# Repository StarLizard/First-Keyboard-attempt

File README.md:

Trying to design my own Bluetooth Keyboard pcb with Hotswap MX Switches

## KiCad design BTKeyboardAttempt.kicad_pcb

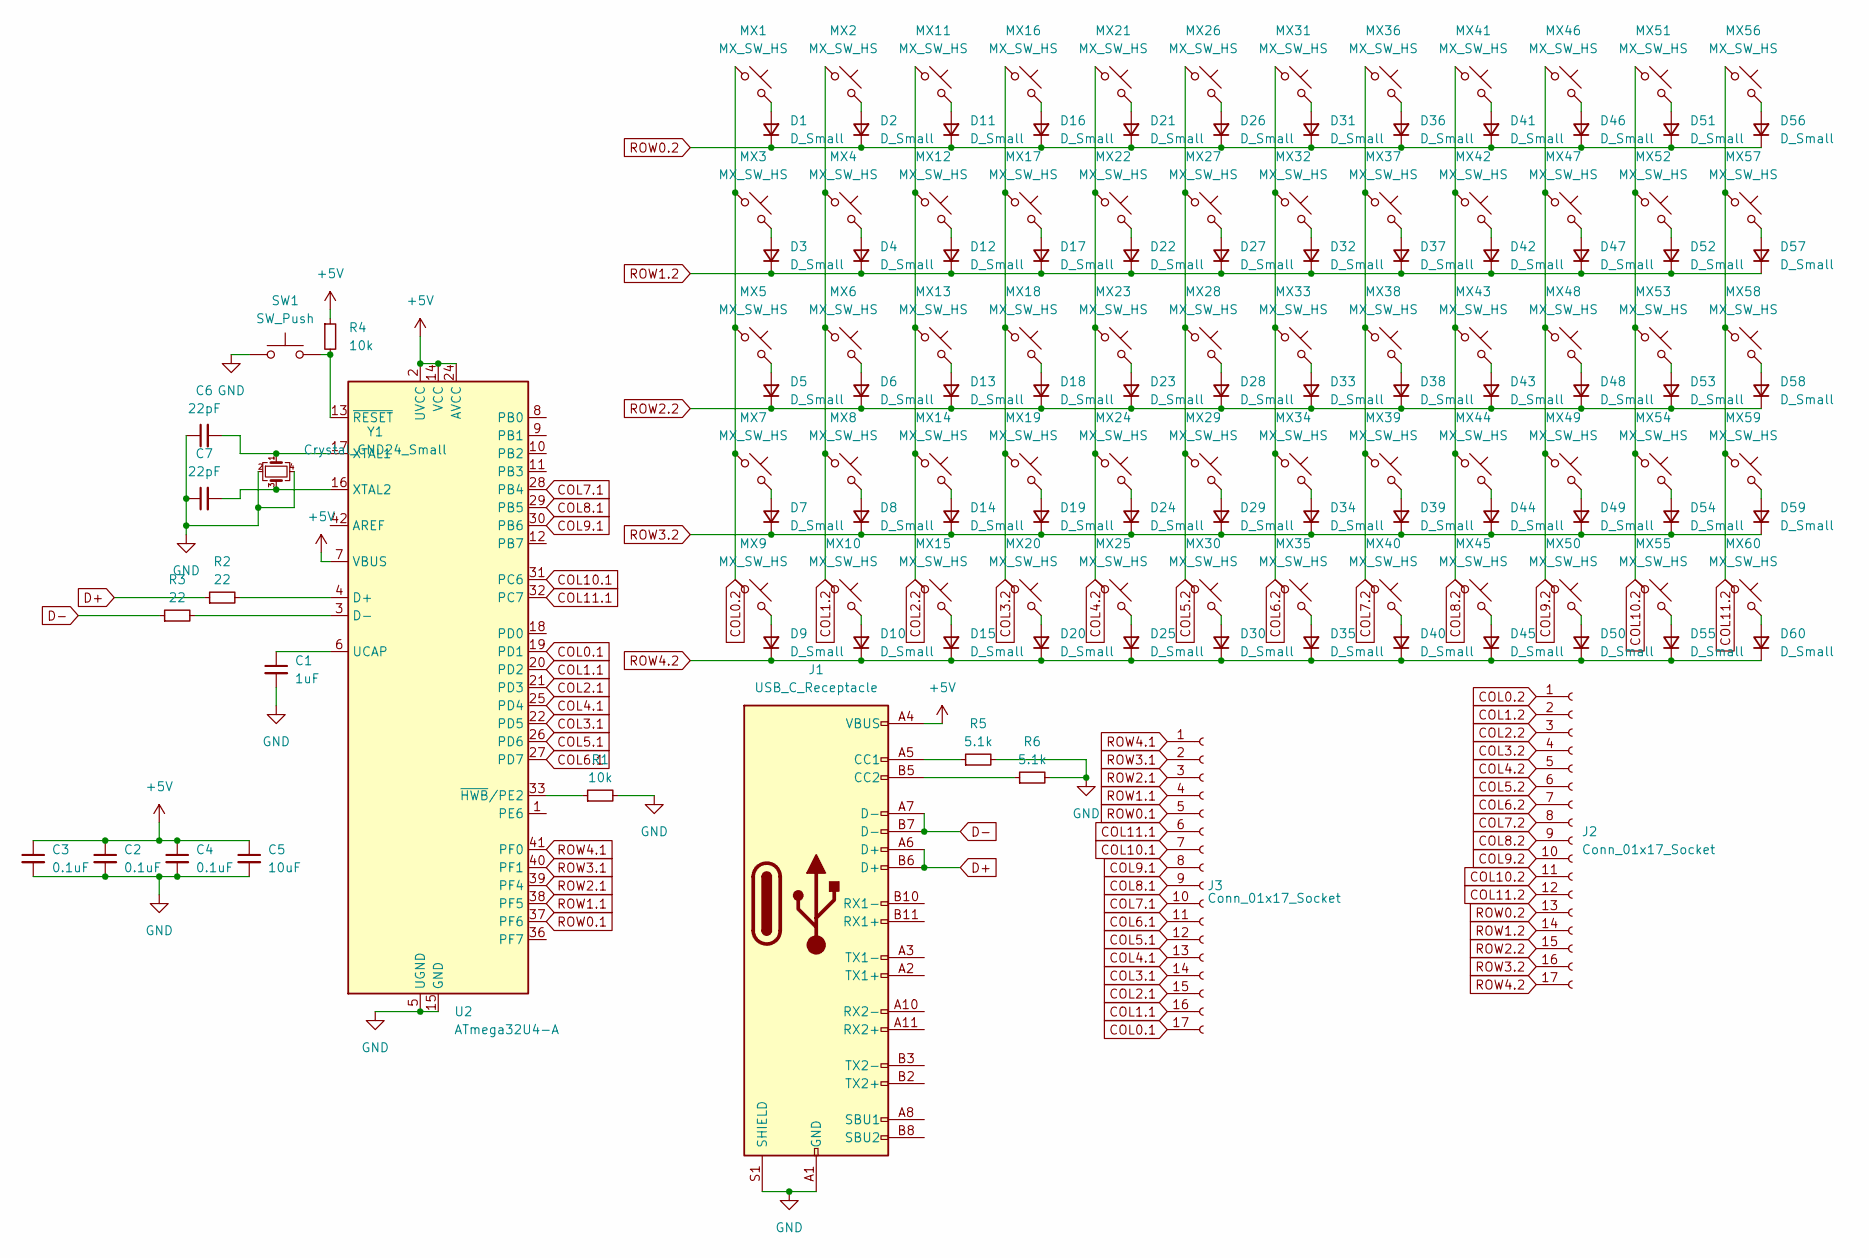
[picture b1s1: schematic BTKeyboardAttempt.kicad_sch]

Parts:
C1: 1uF; C_0805_2012Metric
C2, C3, C4: 0.1uF; C_0805_2012Metric
C5: 10uF; C_0805_2012Metric
C6, C7: 22pF; C_0805_2012Metric
D1, D2, D3, D4, D5, D6, D7, D8, D9, D10, D11, D12, D13, D14, D15, D16, D17, D18, D19, D20, D21, D22, D23, D24, D25, D26, D27, D28, D29, D30, D31, D32, D33, D34, D35, D36, D37, D38, D39, D40, D41, D42, D43, D44, D45, D46, D47, D48, D49, D50, D51, D52, D53, D54, D55, D56, D57, D58, D59, D60: D_Small; D_SOD-123
J1: USB_C_Receptacle; USB_C_Receptacle_Amphenol_12401548E4-2A
J2, J3: Conn_01x17_Socket; PinHeader_1x17_P1.00mm_Horizontal
MX1, MX2, MX3, MX4, MX5, MX6, MX7, MX8, MX9, MX10, MX11, MX12, MX13, MX14, MX15, MX16, MX17, MX18, MX19, MX20, MX21, MX22, MX23, MX24, MX25, MX26, MX27, MX28, MX29, MX30, MX31, MX32, MX33, MX34, MX35, MX36, MX37, MX38, MX39, MX40, MX41, MX42, MX43, MX44, MX45, MX46, MX47, MX48, MX49, MX50, MX51, MX52, MX53, MX54, MX55, MX56, MX57, MX58, MX59, MX60: MX_SW_HS; SW_MX_HS_CPG151101S11_1u
R1, R4: 10k; R_0805_2012Metric
R2, R3: 22; R_0805_2012Metric
R5, R6: 5.1k; R_0805_2012Metric
SW1: SW_Push; SKQG-1155865
U2: ATmega32U4-A; TQFP-44_10x10mm_P0.8mm
Y1: Crystal_GND24_Small; Crystal_SMD_3225-4Pin_3.2x2.5mm

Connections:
+5V: C2.1, C3.1, C4.1, C5.1, J1.A4 (VBUS), J1.A9 (VBUS), J1.B4 (VBUS), J1.B9 (VBUS), R4.1, U2.2 (UVCC), U2.7 (VBUS), U2.14 (VCC), U2.24 (AVCC), U2.34 (VCC), U2.44 (AVCC)
COL0.1: J3.17, U2.19 (PD1)
COL0.2: J2.1, MX1.1, MX3.1, MX5.1, MX7.1, MX9.1
COL1.1: J3.16, U2.20 (PD2)
COL1.2: J2.2, MX2.1, MX4.1, MX6.1, MX8.1, MX10.1
COL2.1: J3.15, U2.21 (PD3)
COL2.2: J2.3, MX11.1, MX12.1, MX13.1, MX14.1, MX15.1
COL3.1: J3.14, U2.22 (PD5)
COL3.2: J2.4, MX16.1, MX17.1, MX18.1, MX19.1, MX20.1
COL4.1: J3.13, U2.25 (PD4)
COL4.2: J2.5, MX21.1, MX22.1, MX23.1, MX24.1, MX25.1
COL5.1: J3.12, U2.26 (PD6)
COL5.2: J2.6, MX26.1, MX27.1, MX28.1, MX29.1, MX30.1
COL6.1: J3.11, U2.27 (PD7)
COL6.2: J2.7, MX31.1, MX32.1, MX33.1, MX34.1, MX35.1
COL7.1: J3.10, U2.28 (PB4)
COL7.2: J2.8, MX36.1, MX37.1, MX38.1, MX39.1, MX40.1
COL8.1: J3.9, U2.29 (PB5)
COL8.2: J2.9, MX41.1, MX42.1, MX43.1, MX44.1, MX45.1
COL9.1: J3.8, U2.30 (PB6)
COL9.2: J2.10, MX46.1, MX47.1, MX48.1, MX49.1, MX50.1
COL10.1: J3.7, U2.31 (PC6)
COL10.2: J2.11, MX51.1, MX52.1, MX53.1, MX54.1, MX55.1
COL11.1: J3.6, U2.32 (PC7)
COL11.2: J2.12, MX56.1, MX57.1, MX58.1, MX59.1, MX60.1
D+: J1.A6 (D+), J1.B6 (D+), R2.1
D-: J1.A7 (D-), J1.B7 (D-), R3.1
GND: C1.2, C2.2, C3.2, C4.2, C5.2, C6.1, C7.1, J1.A1 (GND), J1.A12 (GND), J1.B1 (GND), J1.B12 (GND), J1.S1 (SHIELD), R1.2, R5.2, R6.2, SW1.1, U2.5 (UGND), U2.15 (GND), U2.23 (GND), U2.35 (GND), U2.43 (GND), Y1.2, Y1.4
unnamed: D1.2 (A), MX1.2
unnamed: D2.2 (A), MX2.2
unnamed: D3.2 (A), MX3.2
unnamed: D4.2 (A), MX4.2
unnamed: D5.2 (A), MX5.2
unnamed: D6.2 (A), MX6.2
unnamed: D7.2 (A), MX7.2
unnamed: D8.2 (A), MX8.2
unnamed: D9.2 (A), MX9.2
unnamed: D10.2 (A), MX10.2
unnamed: D11.2 (A), MX11.2
unnamed: D12.2 (A), MX12.2
unnamed: D13.2 (A), MX13.2
unnamed: D14.2 (A), MX14.2
unnamed: D15.2 (A), MX15.2
unnamed: D16.2 (A), MX16.2
unnamed: D17.2 (A), MX17.2
unnamed: D18.2 (A), MX18.2
unnamed: D19.2 (A), MX19.2
unnamed: D20.2 (A), MX20.2
unnamed: D21.2 (A), MX21.2
unnamed: D22.2 (A), MX22.2
unnamed: D23.2 (A), MX23.2
unnamed: D24.2 (A), MX24.2
unnamed: D25.2 (A), MX25.2
unnamed: D26.2 (A), MX26.2
unnamed: D27.2 (A), MX27.2
unnamed: D28.2 (A), MX28.2
unnamed: D29.2 (A), MX29.2
unnamed: D30.2 (A), MX30.2
unnamed: D31.2 (A), MX31.2
unnamed: D32.2 (A), MX32.2
unnamed: D33.2 (A), MX33.2
unnamed: D34.2 (A), MX34.2
unnamed: D35.2 (A), MX35.2
unnamed: D36.2 (A), MX36.2
unnamed: D37.2 (A), MX37.2
unnamed: D38.2 (A), MX38.2
unnamed: D39.2 (A), MX39.2
unnamed: D40.2 (A), MX40.2
unnamed: D41.2 (A), MX41.2
unnamed: D42.2 (A), MX42.2
unnamed: D43.2 (A), MX43.2
unnamed: D44.2 (A), MX44.2
unnamed: D45.2 (A), MX45.2
unnamed: D46.2 (A), MX46.2
unnamed: D47.2 (A), MX47.2
unnamed: D48.2 (A), MX48.2
unnamed: D49.2 (A), MX49.2
unnamed: D50.2 (A), MX50.2
unnamed: D51.2 (A), MX51.2
unnamed: D52.2 (A), MX52.2
unnamed: D53.2 (A), MX53.2
unnamed: D54.2 (A), MX54.2
unnamed: D55.2 (A), MX55.2
unnamed: D56.2 (A), MX56.2
unnamed: D57.2 (A), MX57.2
unnamed: D58.2 (A), MX58.2
unnamed: D59.2 (A), MX59.2
unnamed: D60.2 (A), MX60.2
unnamed: J1.A5 (CC1), R5.1
unnamed: J1.B5 (CC2), R6.1
unnamed: R2.2, U2.4 (D+)
unnamed: R3.2, U2.3 (D-)
unnamed: C1.1, U2.6 (UCAP)
unnamed: C6.2, U2.17 (XTAL1), Y1.1
unnamed: C7.2, U2.16 (XTAL2), Y1.3
unnamed: R1.1, U2.33 (~HWB/PE2)
unnamed: R4.2, SW1.2, U2.13 (~RESET)
ROW0.1: J3.5, U2.37 (PF6)
ROW0.2: D1.1 (K), D2.1 (K), D11.1 (K), D16.1 (K), D21.1 (K), D26.1 (K), D31.1 (K), D36.1 (K), D41.1 (K), D46.1 (K), D51.1 (K), D56.1 (K), J2.13
ROW1.1: J3.4, U2.38 (PF5)
ROW1.2: D3.1 (K), D4.1 (K), D12.1 (K), D17.1 (K), D22.1 (K), D27.1 (K), D32.1 (K), D37.1 (K), D42.1 (K), D47.1 (K), D52.1 (K), D57.1 (K), J2.14
ROW2.1: J3.3, U2.39 (PF4)
ROW2.2: D5.1 (K), D6.1 (K), D13.1 (K), D18.1 (K), D23.1 (K), D28.1 (K), D33.1 (K), D38.1 (K), D43.1 (K), D48.1 (K), D53.1 (K), D58.1 (K), J2.15
ROW3.1: J3.2, U2.40 (PF1)
ROW3.2: D7.1 (K), D8.1 (K), D14.1 (K), D19.1 (K), D24.1 (K), D29.1 (K), D34.1 (K), D39.1 (K), D44.1 (K), D49.1 (K), D54.1 (K), D59.1 (K), J2.16
ROW4.1: J3.1, U2.41 (PF0)
ROW4.2: D9.1 (K), D10.1 (K), D15.1 (K), D20.1 (K), D25.1 (K), D30.1 (K), D35.1 (K), D40.1 (K), D45.1 (K), D50.1 (K), D55.1 (K), D60.1 (K), J2.17

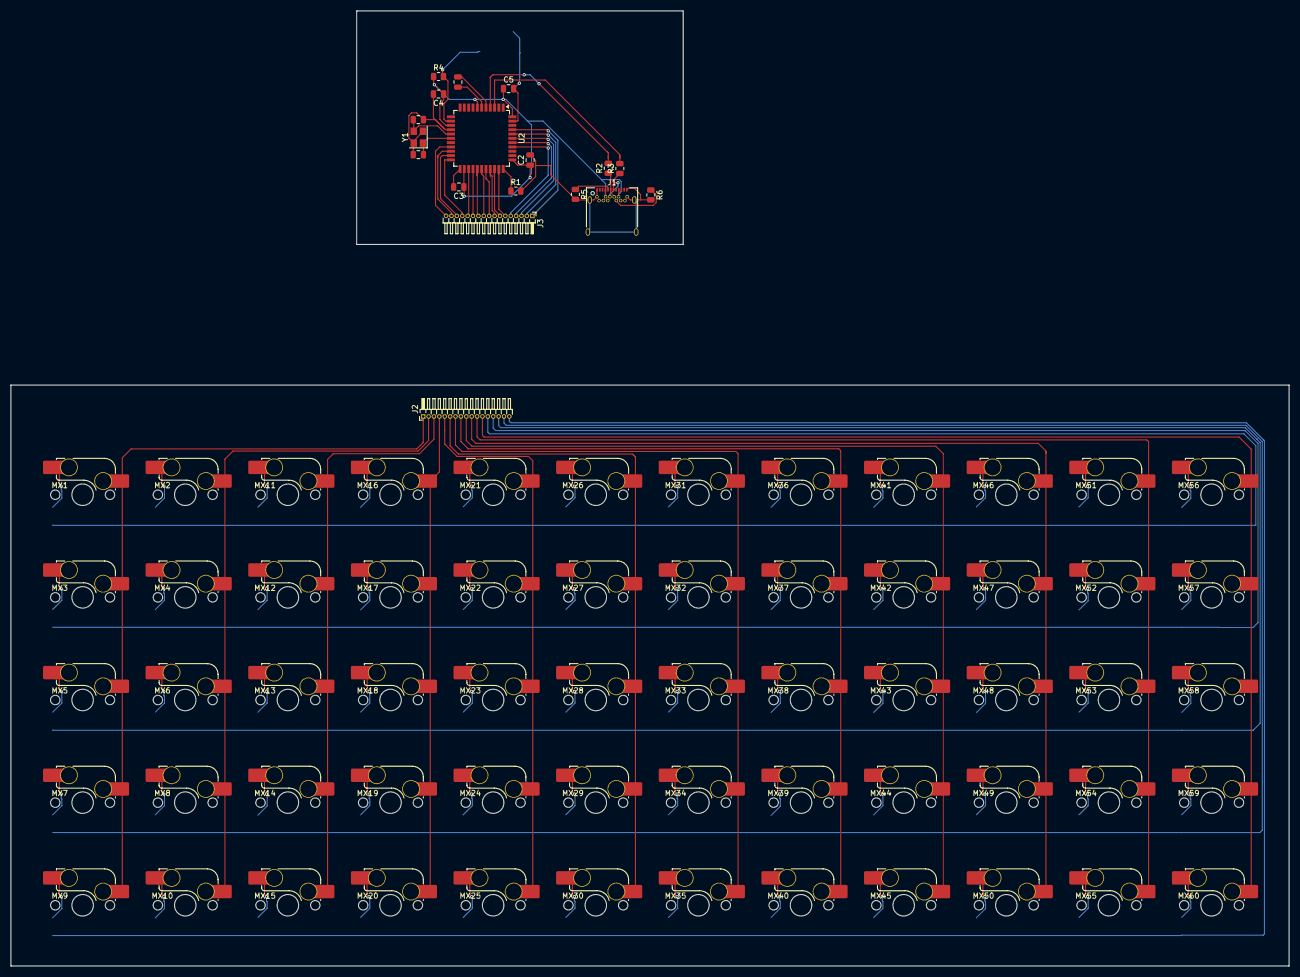
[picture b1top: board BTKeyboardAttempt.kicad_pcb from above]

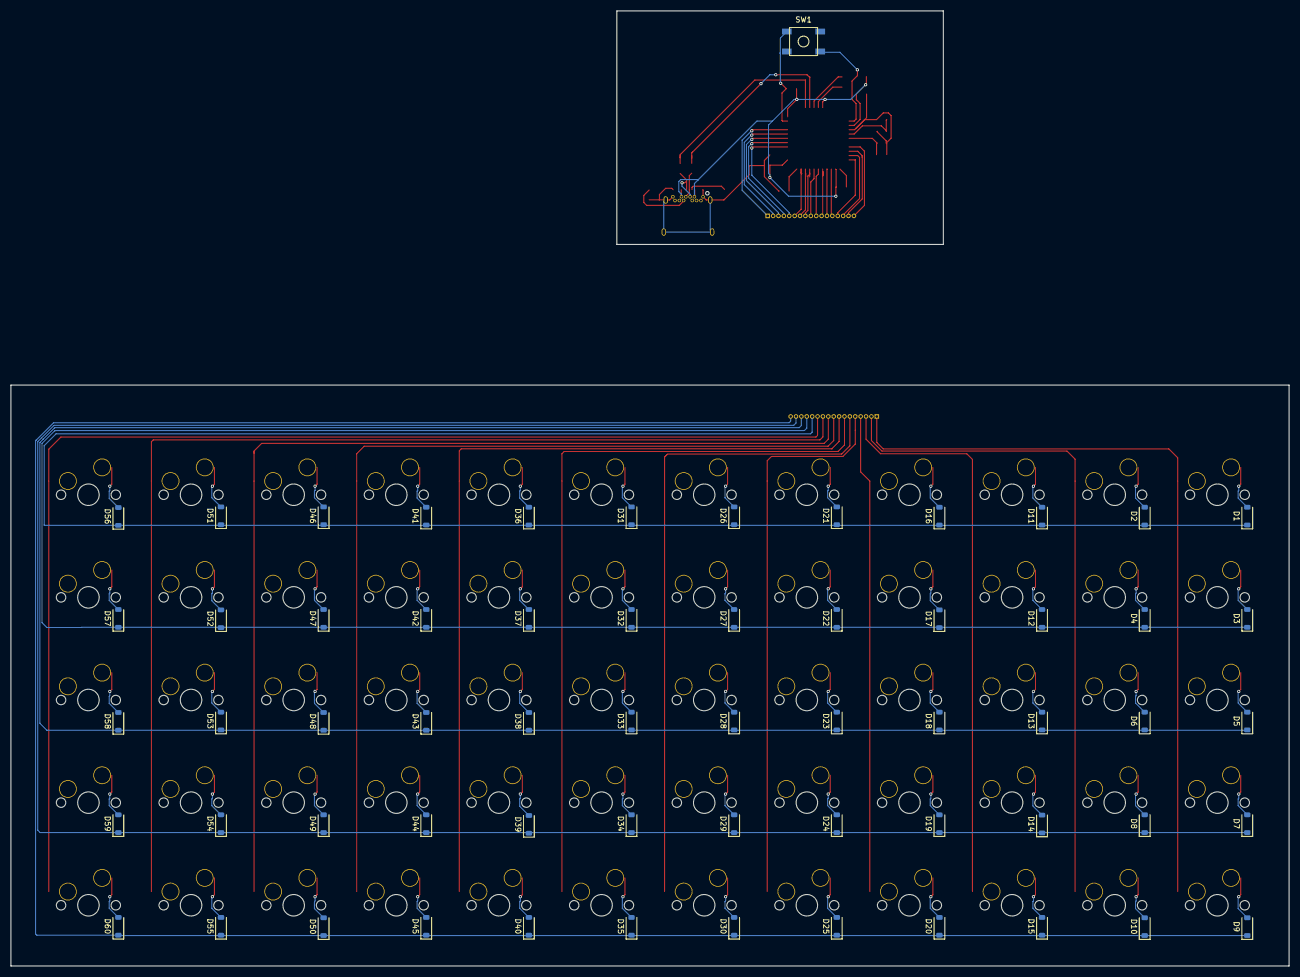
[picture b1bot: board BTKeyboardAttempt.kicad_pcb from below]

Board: 2 copper layers, 237.2 x 107.8 mm, 139 parts (61 on the bottom side), 107 nets.

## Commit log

2024-09-01 MCU Schem
2024-09-01 add submodules
2024-09-01 add lib
2024-09-01 schematic complete pcb updated
2024-09-01 Switch and Diode Routing
2024-09-02 Finished?
2024-09-02 idk what even changed
2024-09-02 Daughter board
    Put MCU and USB-C (+assoc. bits) on a daughter board to reduce overall footprint of pcb
2024-09-03 lil bit of refining
